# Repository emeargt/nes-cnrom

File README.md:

# nes-cnrom
[![CC BY-SA 4.0][cc-by-sa-shield]][cc-by-sa]

[cc-by-sa]: http://creativecommons.org/licenses/by-sa/4.0/
[cc-by-sa-shield]: https://img.shields.io/badge/License-CC%20BY--SA%204.0-lightgrey.svg

This repository contains a KiCad project for a NES-CN-ROM-256-05 cartridge pcb.

Original NES-CN-ROM-256-05 schematic is from N. Schenk's [NES repo](https://github.com/schenkzoola/NES/tree/main/Cartridges/NES/NES-CN-ROM-256-05). The schematic was modified to include currently available parts and their associated footprints.

The board matches the dimensions of the original and will idealy fit in standard or reproduction shells. A list of parts to populate the board can be found in the bom directory.

## Build Guide
There is a basic [build guide](./docs/buildguide.md) that provides some tips and resources for bringing up a board.

## Memory Support
v02 was designed to support the SST39SF0x0A series of 32 DIP flash chips. However, the AT27CxxxR series of 28 DIP EPROMs have a very similar pinout and should work on the board by mapping pin 1 of the EPROM to pin 3 of the 32 DIP footprint. Other 28 DIP memory chips may work as well, but their pinouts should be compared to that of the SST39SF0x0A to be certain.

## Schematic

## Board Layout
Top | Bottom
:---: | :---:
 | 

Board render (front):

## Changelog

### [v02]
- New board layout to support 32 DIP flash chips (SST39SF0x0A)
- Add isometric logo design
- Increase board dimensions

### [v01.1]
- Connected pins 57 and 58 on the cartridge edge connector for internal VRAM enable.

### [v01]
- Initial schematic and board layout.

[v02]: https://github.com/emeargt/nes-cnrom/releases/tag/v02
[v01.1]: https://github.com/emeargt/nes-cnrom/releases/tag/v01.1
[v01]: https://github.com/emeargt/nes-cnrom/releases/tag/v01-alpha

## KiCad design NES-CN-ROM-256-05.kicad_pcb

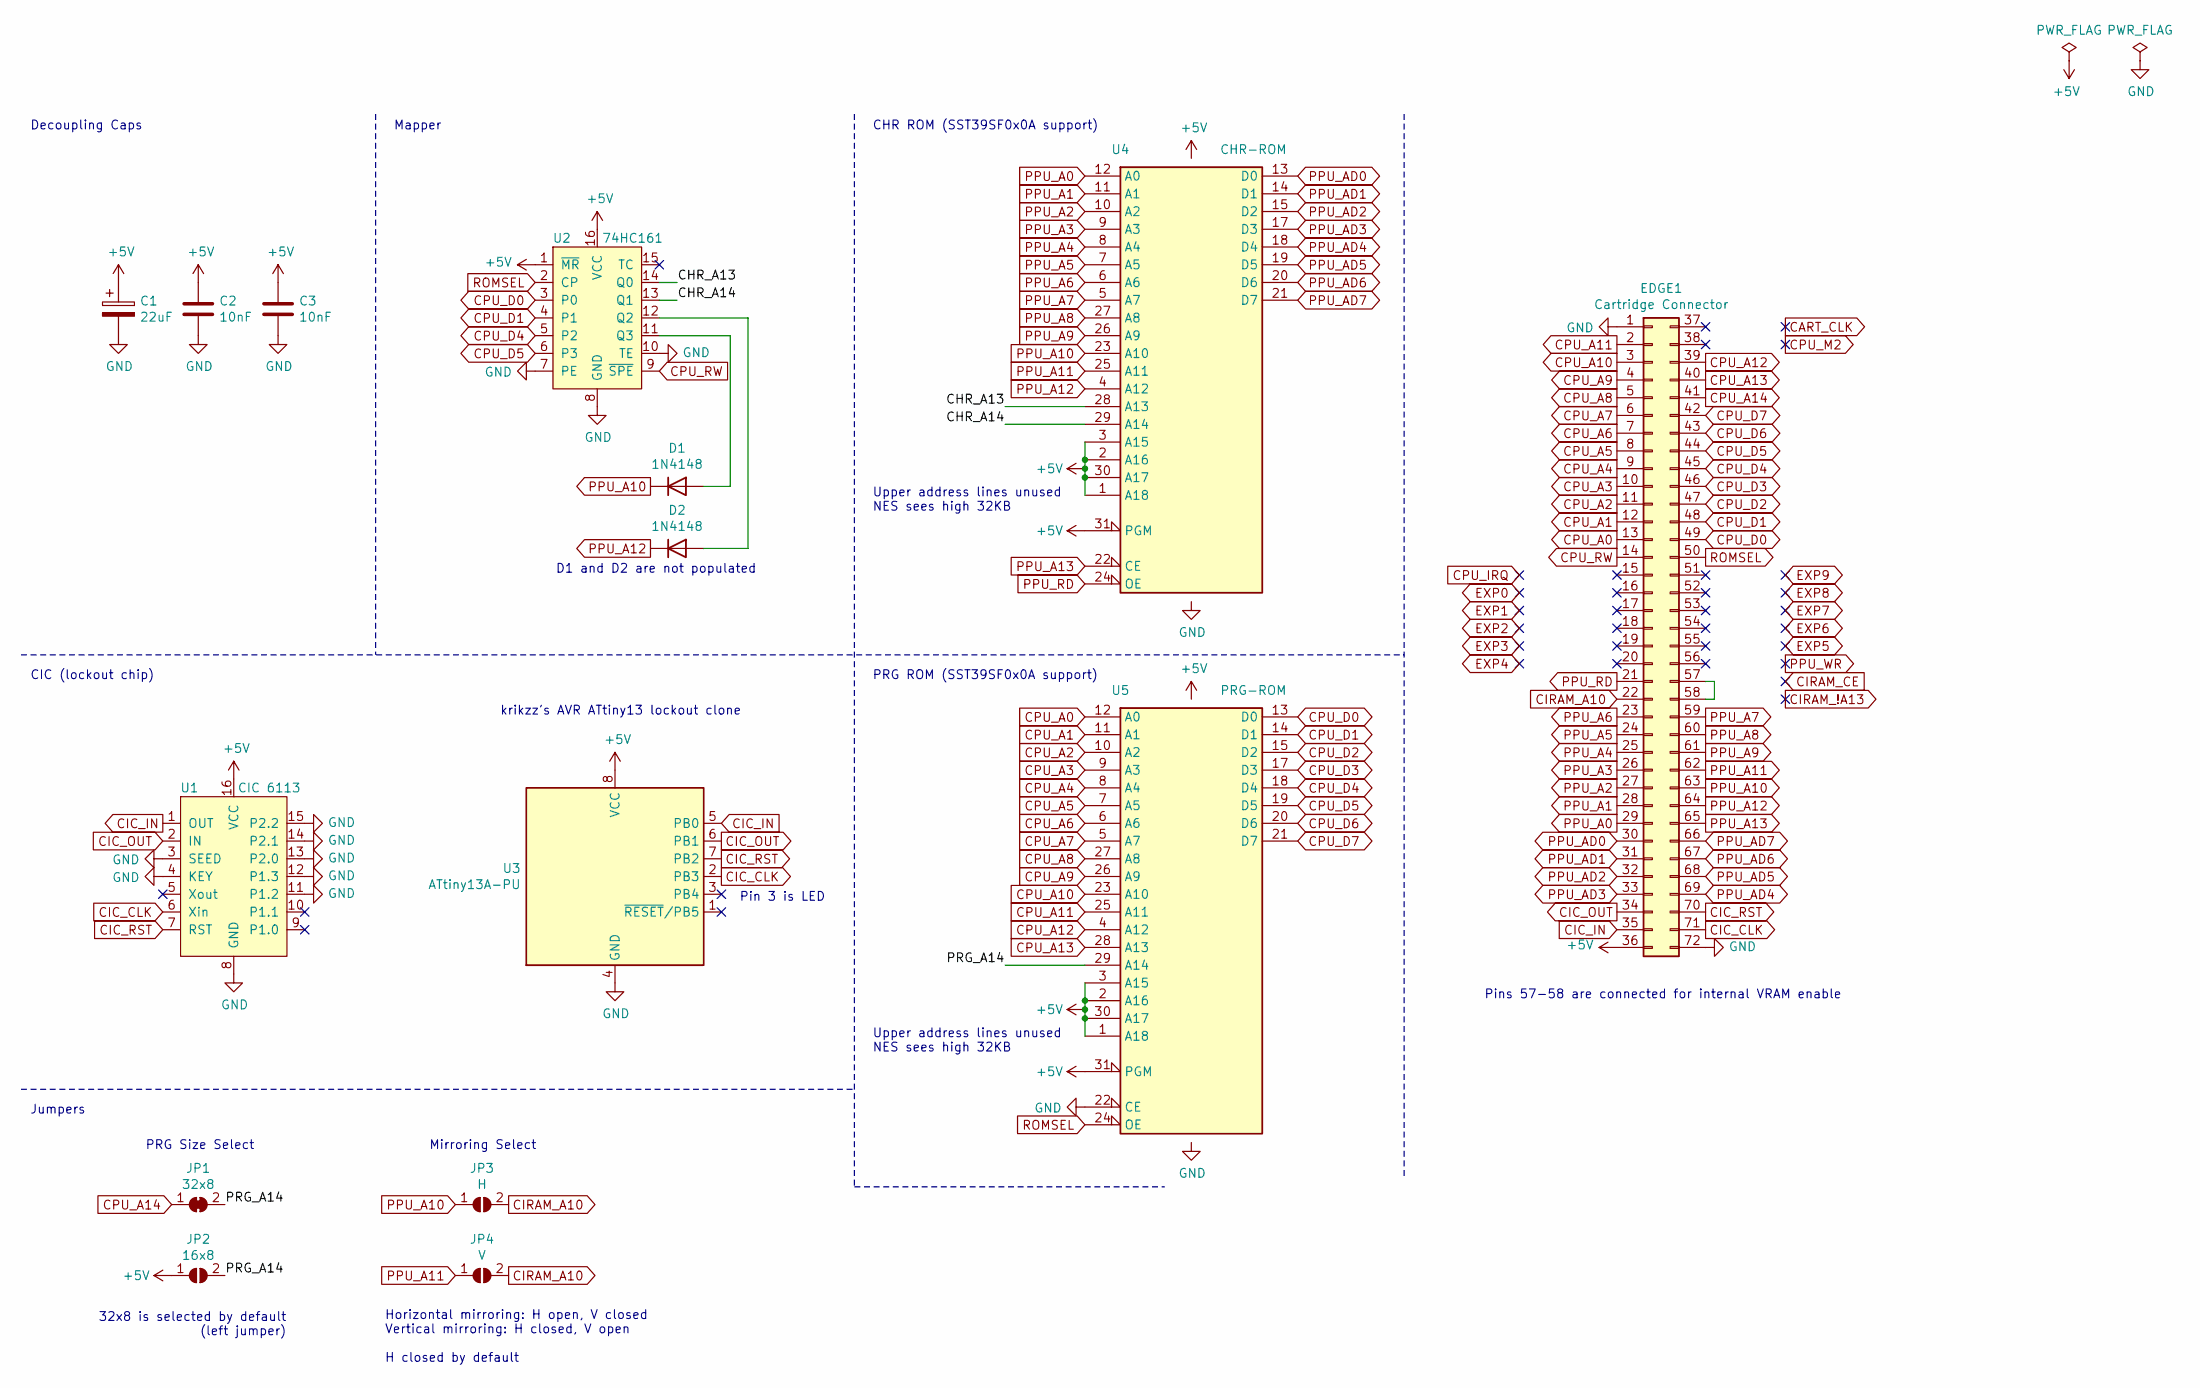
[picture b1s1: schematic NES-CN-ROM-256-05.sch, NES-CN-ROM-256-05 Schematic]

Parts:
C1: 22uF; CP_Radial_D4.0mm_P1.50mm
C2, C3: 10nF; C_Axial_L5.1mm_D3.1mm_P7.50mm_Horizontal
D1, D2: 1N4148; D_DO-35_SOD27_P7.62mm_Horizontal
EDGE1: Cartridge Connector; cartridge_edge_72
JP1: 32x8; SolderJumper-2_P1.3mm_Bridged_RoundedPad1.0x1.5mm
JP2: 16x8; SolderJumper-2_P1.3mm_Open_RoundedPad1.0x1.5mm
JP3: H; SolderJumper-2_P1.3mm_Open_RoundedPad1.0x1.5mm
JP4: V; SolderJumper-2_P1.3mm_Open_RoundedPad1.0x1.5mm
U1: CIC 6113; DIP-16_W7.62mm
U2: 74HC161; DIP-16_W7.62mm
U3: ATtiny13A-PU; DIP-8_W7.62mm
U4: CHR-ROM; DIP-32_W15.24mm
U5: PRG-ROM; DIP-32_W15.24mm

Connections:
+5V: C1.1, C2.1, C3.1, EDGE1.36, JP2.1 (A), U1.16 (VCC), U2.1 (~MR), U2.16 (VCC), U3.8 (VCC), U4.1 (A18), U4.2 (A16), U4.3 (A15), U4.30 (A17), U4.31 (PGM), U4.32 (VCC), U5.1 (A18), U5.2 (A16), U5.3 (A15), U5.30 (A17), U5.31 (PGM), U5.32 (VCC)
/CHR_A13: U2.14 (Q0), U4.28 (A13)
/CHR_A14: U2.13 (Q1), U4.29 (A14)
/PRG_A14: JP1.2 (B), JP2.2 (B), U5.29 (A14)
CIC_CLK: EDGE1.71, U1.6 (Xin), U3.2 (PB3)
CIC_IN: EDGE1.35, U1.1 (OUT), U3.5 (PB0)
CIC_OUT: EDGE1.34, U1.2 (IN), U3.6 (PB1)
CIC_RST: EDGE1.70, U1.7 (RST), U3.7 (PB2)
CIRAM_A10: EDGE1.22, JP3.2 (B), JP4.2 (B)
CPU_A0: EDGE1.13, U5.12 (A0)
CPU_A1: EDGE1.12, U5.11 (A1)
CPU_A2: EDGE1.11, U5.10 (A2)
CPU_A3: EDGE1.10, U5.9 (A3)
CPU_A4: EDGE1.9, U5.8 (A4)
CPU_A5: EDGE1.8, U5.7 (A5)
CPU_A6: EDGE1.7, U5.6 (A6)
CPU_A7: EDGE1.6, U5.5 (A7)
CPU_A8: EDGE1.5, U5.27 (A8)
CPU_A9: EDGE1.4, U5.26 (A9)
CPU_A10: EDGE1.3, U5.23 (A10)
CPU_A11: EDGE1.2, U5.25 (A11)
CPU_A12: EDGE1.39, U5.4 (A12)
CPU_A13: EDGE1.40, U5.28 (A13)
CPU_A14: EDGE1.41, JP1.1 (A)
CPU_D0: EDGE1.49, U2.3 (P0), U5.13 (D0)
CPU_D1: EDGE1.48, U2.4 (P1), U5.14 (D1)
CPU_D2: EDGE1.47, U5.15 (D2)
CPU_D3: EDGE1.46, U5.17 (D3)
CPU_D4: EDGE1.45, U2.5 (P2), U5.18 (D4)
CPU_D5: EDGE1.44, U2.6 (P3), U5.19 (D5)
CPU_D6: EDGE1.43, U5.20 (D6)
CPU_D7: EDGE1.42, U5.21 (D7)
CPU_RW: EDGE1.14, U2.9 (~SPE)
GND: C1.2, C2.2, C3.2, EDGE1.1, EDGE1.72, U1.3 (SEED), U1.4 (KEY), U1.8 (GND), U1.11 (P1.2), U1.12 (P1.3), U1.13 (P2.0), U1.14 (P2.1), U1.15 (P2.2), U2.7 (PE), U2.8 (GND), U2.10 (TE), U3.4 (GND), U4.16 (GND), U5.16 (GND), U5.22 (CE)
unnamed: D1.2 (A), U2.11 (Q3)
unnamed: D2.2 (A), U2.12 (Q2)
unnamed: EDGE1.57, EDGE1.58
PPU_A0: EDGE1.29, U4.12 (A0)
PPU_A1: EDGE1.28, U4.11 (A1)
PPU_A2: EDGE1.27, U4.10 (A2)
PPU_A3: EDGE1.26, U4.9 (A3)
PPU_A4: EDGE1.25, U4.8 (A4)
PPU_A5: EDGE1.24, U4.7 (A5)
PPU_A6: EDGE1.23, U4.6 (A6)
PPU_A7: EDGE1.59, U4.5 (A7)
PPU_A8: EDGE1.60, U4.27 (A8)
PPU_A9: EDGE1.61, U4.26 (A9)
PPU_A10: D1.1 (K), EDGE1.63, JP3.1 (A), U4.23 (A10)
PPU_A11: EDGE1.62, JP4.1 (A), U4.25 (A11)
PPU_A12: D2.1 (K), EDGE1.64, U4.4 (A12)
PPU_A13: EDGE1.65, U4.22 (CE)
PPU_AD0: EDGE1.30, U4.13 (D0)
PPU_AD1: EDGE1.31, U4.14 (D1)
PPU_AD2: EDGE1.32, U4.15 (D2)
PPU_AD3: EDGE1.33, U4.17 (D3)
PPU_AD4: EDGE1.69, U4.18 (D4)
PPU_AD5: EDGE1.68, U4.19 (D5)
PPU_AD6: EDGE1.67, U4.20 (D6)
PPU_AD7: EDGE1.66, U4.21 (D7)
PPU_RD: EDGE1.21, U4.24 (OE)
ROMSEL: EDGE1.50, U2.2 (CP), U5.24 (OE)

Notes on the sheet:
32x8 is selected by default (left jumper)
D1 and D2 are not populated
CHR ROM (SST39SF0x0A support)
PRG ROM (SST39SF0x0A support)
Mapper
Decoupling Caps
CIC (lockout chip)
Jumpers
krikzz's AVR ATtiny13 lockout clone
Mirroring Select
PRG Size Select
Pin 3 is LED
Horizontal mirroring: H open, V closed Vertical mirroring: H closed, V open H closed by default
Pins 57-58 are connected for internal VRAM enable
Upper address lines unused NES sees high 32KB

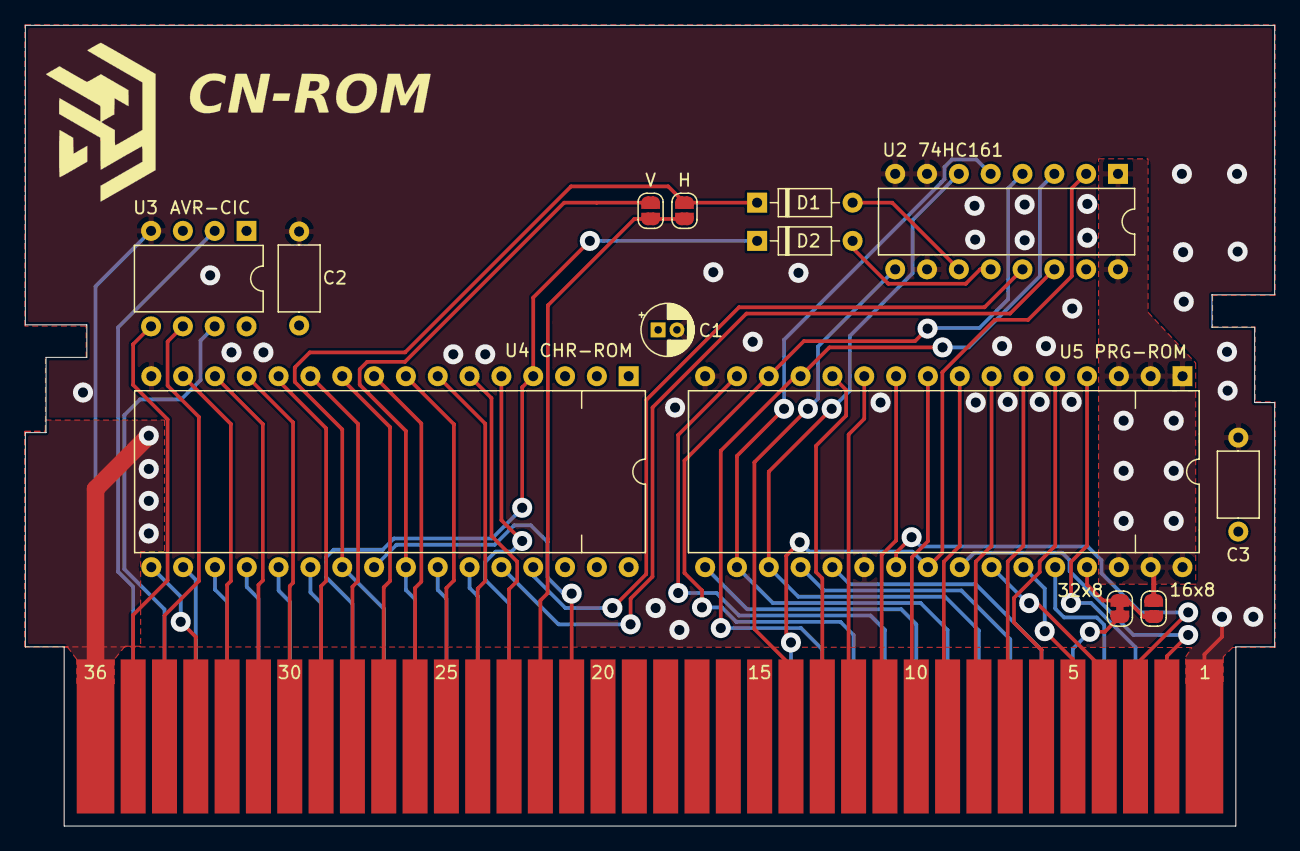
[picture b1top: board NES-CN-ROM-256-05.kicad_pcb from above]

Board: 2 copper layers, 99.7 x 63.9 mm, 17 parts (0 on the bottom side), 61 nets.

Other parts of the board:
G1: LOGO; flash_logo
G2: LOGO; flash_negative_logo
G3: LOGO; cnrom_text

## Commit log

2022-04-26 Add shematic image
2022-04-26 Add cc-by-sa license and put shield in readme
2022-04-26 Fix license shield in readme
2022-04-26 [1] Change gerbers to protel file ext [2] Fix board dimensions [3] Add screenshot of jlcpcb order settings
2022-04-28 Add schematic attribution to readme
2022-06-10 [1] Connect cartridge pins 57-58 for NES internal VRAM enable line. [2] Regenerate gerbers.
2022-06-10 Update readme with v01.1 changes
2022-07-30 New board layout to support 32 dip flash chips
2022-07-30 [1] Update changelog in readme with v02 notes. [2] Add memory support section to readme.
2022-07-31 Add board dimension increase note to changelog
2022-10-08 Adding build guide
2022-10-08 Add build guide section and link to readme

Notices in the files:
NES-CN-ROM-256-05.kicad_pcb:
License: https://creativecommons.org/licenses/by-sa/4.0
